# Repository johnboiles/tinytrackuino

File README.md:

Tiny Trackuino
==============
http://github.com/johnboiles/tinytrackuino

Small [Trackuino](http://www.trackuino.org/)-compatible board for transmitting APRS packets over 2m amateur radio.

Firmware
--------
The firmware is available at [github.com/johnboiles/trackuino](http://github.com/johnboiles/trackuino). It is modified from the [original Trackuino firmware](https://code.google.com/p/trackuino/) in order to support the newer 32u4 processors.

Bill of Materials
-----------------
2x [Screw Terminals 3.5mm Pitch (2-Pin)](https://www.sparkfun.com/products/8084)

1x [Screw Terminals 3.5mm Pitch (3-Pin)](https://www.sparkfun.com/products/8235)

1x [Arduino Pro Micro](https://www.sparkfun.com/products/11098)

1x [Female Headers](https://www.sparkfun.com/products/115)

1x [Break Away Headers](https://www.sparkfun.com/products/116)

1x [SMA Female Thru Hole Connector](https://www.sparkfun.com/products/593)

1x [EM406 (JST-SH) Horizontal Connector](https://www.sparkfun.com/products/10210)

1x [5V GPS with JST-SH connector](https://www.sparkfun.com/products/11571)

1x [JST-SH Cable](https://www.sparkfun.com/products/9123)

1x [Thru-hole Button](https://www.sparkfun.com/products/97)

1x [Radiometrix HX1 Transmitter](http://www.radiometrix.com/content/hx1)

2x [LM60 Temperature Sensor](http://www.digikey.com/scripts/DKSearch/dksus.dll?Detail&itemSeq=136296865&uq=635144426529530060)

2x [SOT23 N-Channel Mosfet](http://www.digikey.com/scripts/DKSearch/dksus.dll?Detail&itemSeq=136296519&uq=635144426529530060)

1x 10k Resistor 0603

1x 3.3k Resistor 0603

1x 1k Resistor 0603

2x 10uF Capacitor 1206

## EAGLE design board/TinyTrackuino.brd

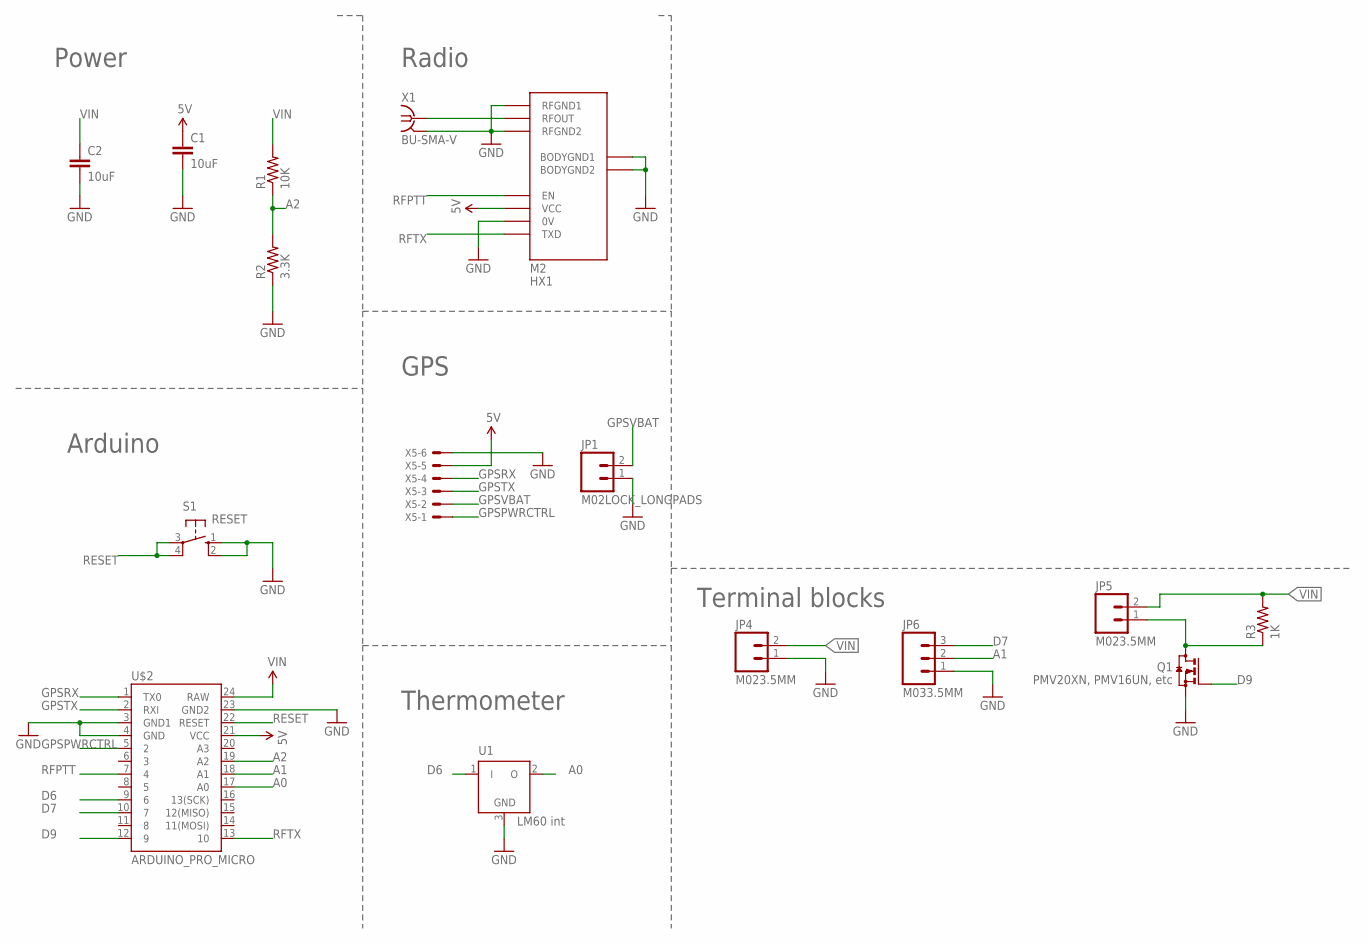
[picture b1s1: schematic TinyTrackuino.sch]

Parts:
C1, C2: 10uF; 1206
JP1: M02LOCK_LONGPADS; 1X02_LOCK_LONGPADS
JP4, JP5: M023.5MM; SCREWTERMINAL-3.5MM-2
JP6: M033.5MM; SCREWTERMINAL-3.5MM-3
M2: HX1
Q1: PMV20XN, PMV16UN, etc; SOT23
R1: 10K; 0603-RES
R2: 3.3K; 0603-RES
R3: 1K; 0603-RES
S1: RESET; B3F-10XX
U1: LM60 int; TO92
U$2: ARDUINO_PRO_MICRO
X1: BU-SMA-V
X5: SM06B-SRSS-TB

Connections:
5V: C1.1, M2.VCC, U$2.21 (VCC), X5.5
A0: U1.2 (O), U$2.17 (A0)
A1: JP6.2, U$2.18 (A1)
A2: R1.1, R2.2, U$2.19 (A2)
D6: U1.1 (I), U$2.9 (6)
D7: JP6.3, U$2.10 (7)
D9: Q1.1 (G), U$2.12 (9)
GND: C1.2, C2.2, JP1.1, JP4.1, JP6.1, M2.0V, M2.BODYGND1, M2.BODYGND2, M2.RFGND1, M2.RFGND2, Q1.2 (S), R2.1, S1.1 (S), S1.2 (S1), U1.3 (GND), U$2.3 (GND1), U$2.4 (GND), U$2.23 (GND2), X1.2 (GND), X1.3 (GND), X1.4 (GND), X1.5 (GND), X5.6
GPSPWRCTRL: U$2.5 (2), X5.1
GPSRX: U$2.1 (TX0), X5.4
GPSTX: U$2.2 (RXI), X5.3
GPSVBAT: JP1.2, X5.2
unnamed: JP5.1, Q1.3 (D), R3.1
RESET: S1.3, S1.4 (P1), U$2.22 (RESET)
RFOUT: M2.RFOUT, X1.1
RFPTT: M2.EN, U$2.7 (4)
RFTX: M2.TXD, U$2.13 (10)
VIN: C2.1, JP4.2, JP5.2, R1.2, R3.2, U$2.24 (RAW)

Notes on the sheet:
Power
Arduino
Radio
GPS
Thermometer
Terminal blocks

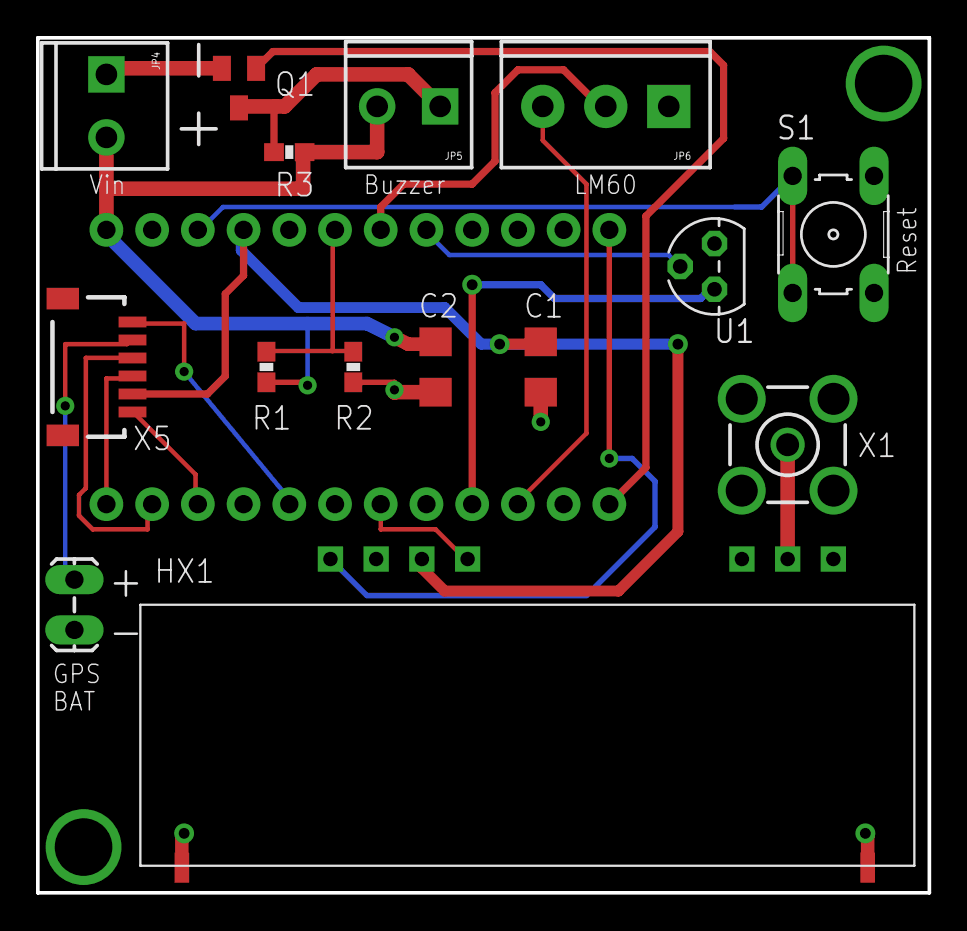
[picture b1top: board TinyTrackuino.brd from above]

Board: 2 copper layers, 49.5 x 47.5 mm, 16 parts (0 on the bottom side), 18 nets.

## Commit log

2013-08-29 Fixing temp sensor silkscreen and gps connector
2013-09-04 Almost final revision of board
2013-09-07 Possibly final commit for revision 1
2013-09-11 Using 3.5mm screw terminals instead of 5mm
2013-09-11 Moving Vin to edge of board
2013-09-11 Adding license and readme files

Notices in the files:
parts and their libraries:
SparkFun-Boards: Licensing: CC v3.0 Share-Alike You are welcome to use this library for commercial purposes.
